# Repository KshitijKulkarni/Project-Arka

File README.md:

# Project-Arka
The project code base is split on two folders
1. Microcontroller Code - All code that will be run/tested on microcontrollers (Teensy 4.1, Arduino UNO etc)
2. Ground Control Code - All code that will be run on a system external to the engine (includes code for the GUI)

## Microcontroller Code
The files in this folder are sorted as follows
```
Microcontroller Code
├── moduleTestCodes
└── <microcontrollerBoardname>
    ├── <microcontrollerBoardname>.ino
    └── src
        ├── HelperModule1
        │   ├── HelperModule1.h
        │   └── HelperModule1.cpp
        ├── HelperModule2
        │   ├── HelperModule2.h
        │   └── HelperModule2.cpp
        └── HelperModule3
            ├── HelperModule3.h
            └── HelperModule3.cpp
```

The moduleTestCodes directory contains code for testing individual sensor/motor modules, which are not directly suitable for reuse in the final project.

## Ground Control Code

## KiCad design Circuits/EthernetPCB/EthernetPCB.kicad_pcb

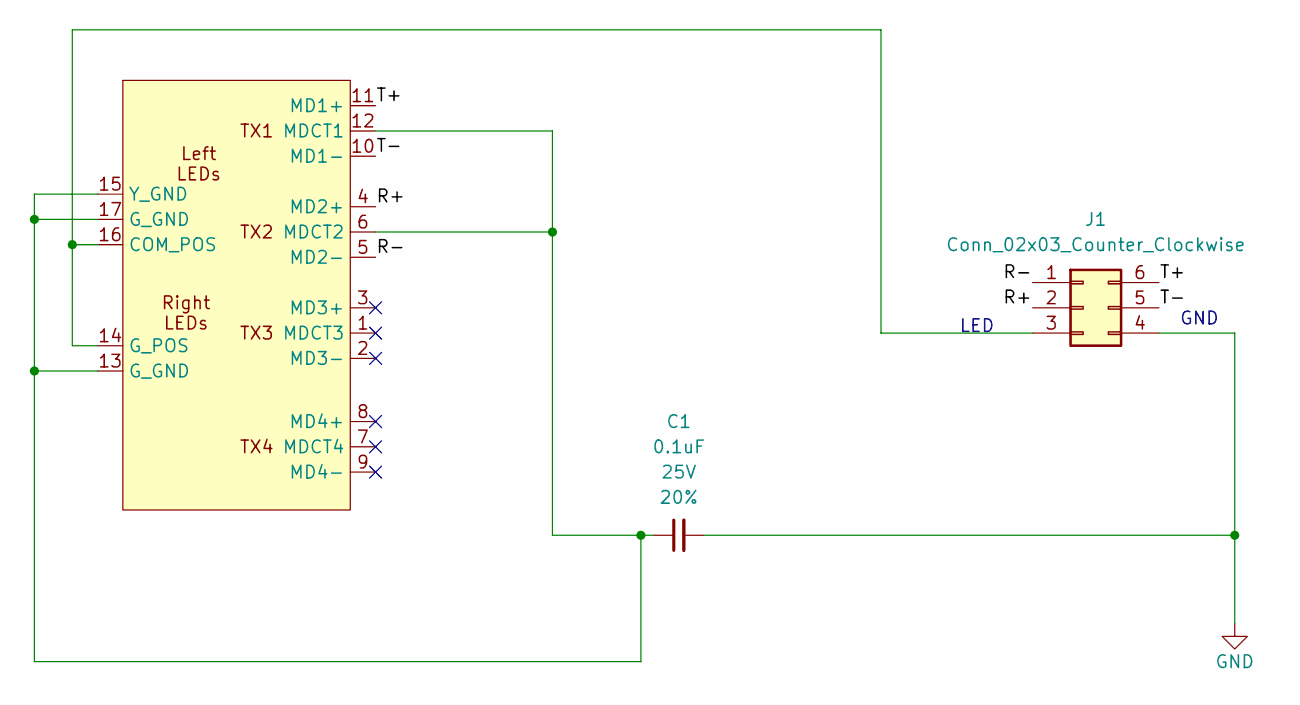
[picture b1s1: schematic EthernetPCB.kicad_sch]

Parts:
C1: 0.1uF; C_Disc_D3.0mm_W2.0mm_P2.50mm; Voltage 25V; Tolerance 20%
J1: Conn_02x03_Counter_Clockwise; PinHeader_2x03_P2.54mm_Vertical
U1: LINK-PP LPJK7003B97NL

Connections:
/R+: J1.2, U1.4 (MD2+)
/R-: J1.1, U1.5 (MD2-)
/T+: J1.6, U1.11 (MD1+)
/T-: J1.5, U1.10 (MD1-)
GND: C1.2, J1.4
unnamed: J1.3, U1.14 (G_POS), U1.16 (COM_POS)
unnamed: C1.1, U1.6 (MDCT2), U1.12 (MDCT1), U1.13 (G_GND), U1.15 (Y_GND), U1.17 (G_GND)

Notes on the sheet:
LED
GND

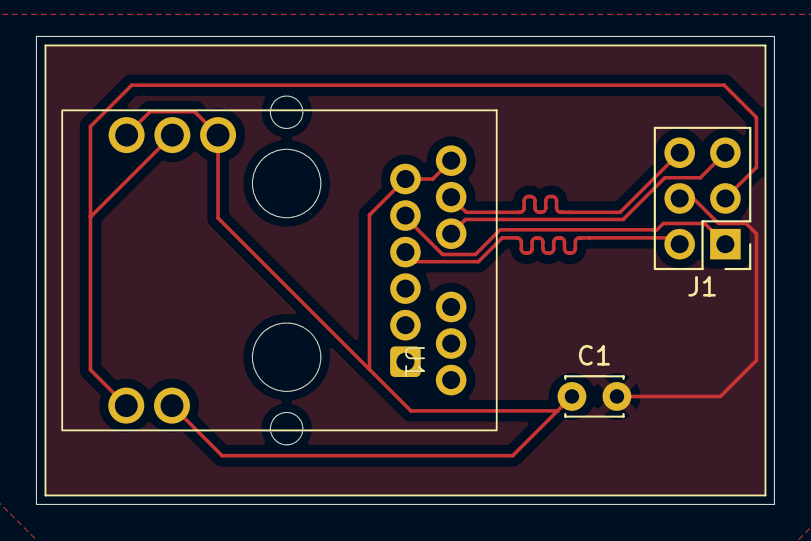
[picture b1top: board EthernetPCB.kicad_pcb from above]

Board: 2 copper layers, 41.0 x 26.0 mm, 3 parts (0 on the bottom side), 7 nets.

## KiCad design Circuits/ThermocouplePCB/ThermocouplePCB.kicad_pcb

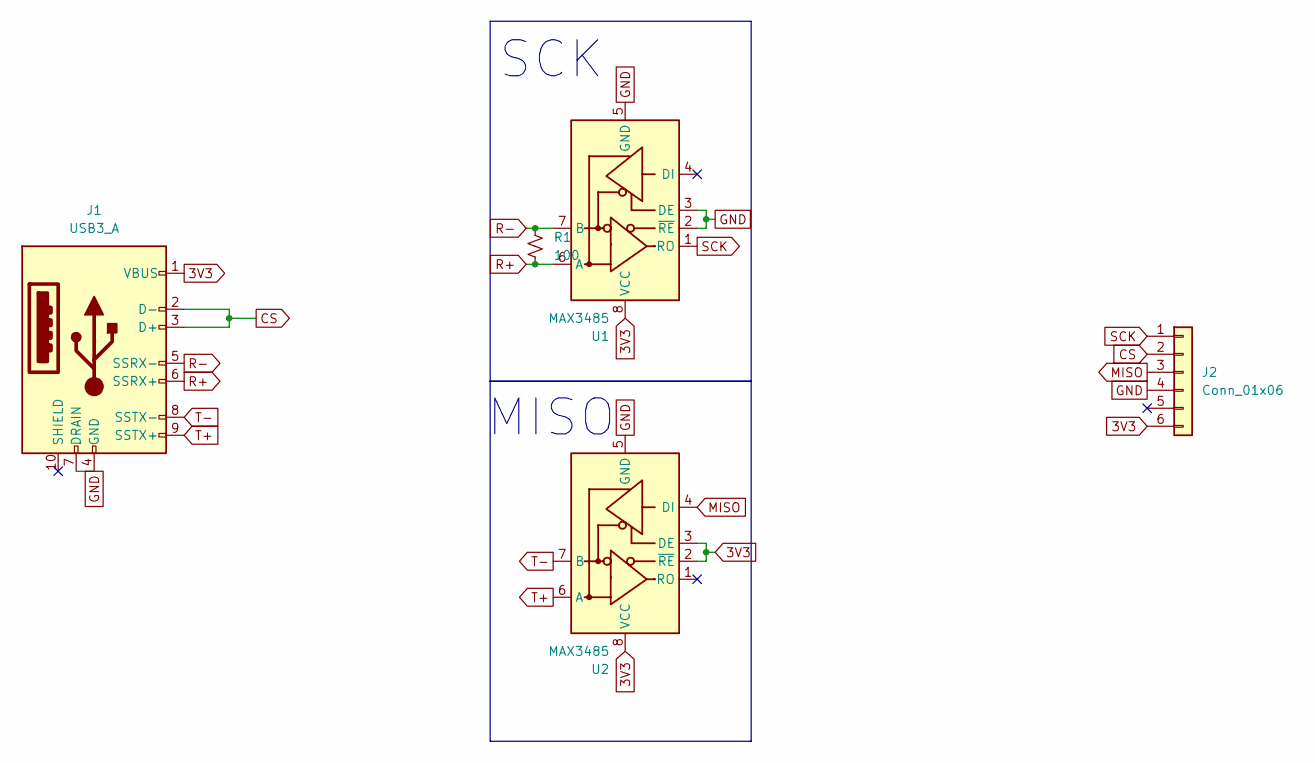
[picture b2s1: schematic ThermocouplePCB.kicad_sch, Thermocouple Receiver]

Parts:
J1: USB3_A; SAMTEC_USB3-A-S-F-TH
J2: Conn_01x06; PinSocket_1x06_P2.54mm_Vertical
R1: 100; R_Axial_DIN0207_L6.3mm_D2.5mm_P7.62mm_Horizontal
U1, U2: MAX3485; SOIC-8_3.9x4.9mm_P1.27mm

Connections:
3V3: J1.1 (VBUS), J2.6, U1.8 (VCC), U2.2 (~RE), U2.3 (DE), U2.8 (VCC)
CS: J1.2 (D-), J1.3 (D+), J2.2
GND: J1.4 (GND), J1.7 (DRAIN), J2.4, U1.2 (~RE), U1.3 (DE), U1.5 (GND), U2.5 (GND)
MISO: J2.3, U2.4 (DI)
R+: J1.6 (SSRX+), R1.1, U1.6 (A)
R-: J1.5 (SSRX-), R1.2, U1.7 (B)
SCK: J2.1, U1.1 (RO)
T+: J1.9 (SSTX+), U2.6 (A)
T-: J1.8 (SSTX-), U2.7 (B)

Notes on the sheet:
SCK
MISO

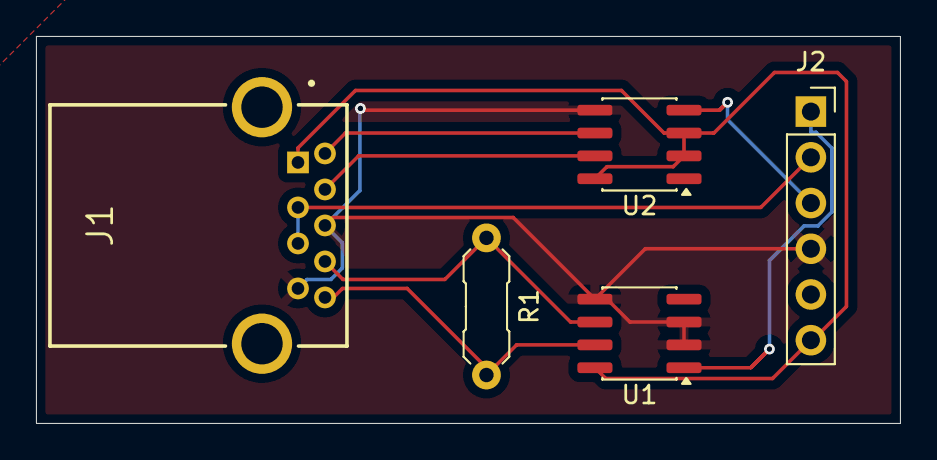
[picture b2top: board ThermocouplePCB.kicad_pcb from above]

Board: 2 copper layers, 48.0 x 21.5 mm, 5 parts (0 on the bottom side), 9 nets.

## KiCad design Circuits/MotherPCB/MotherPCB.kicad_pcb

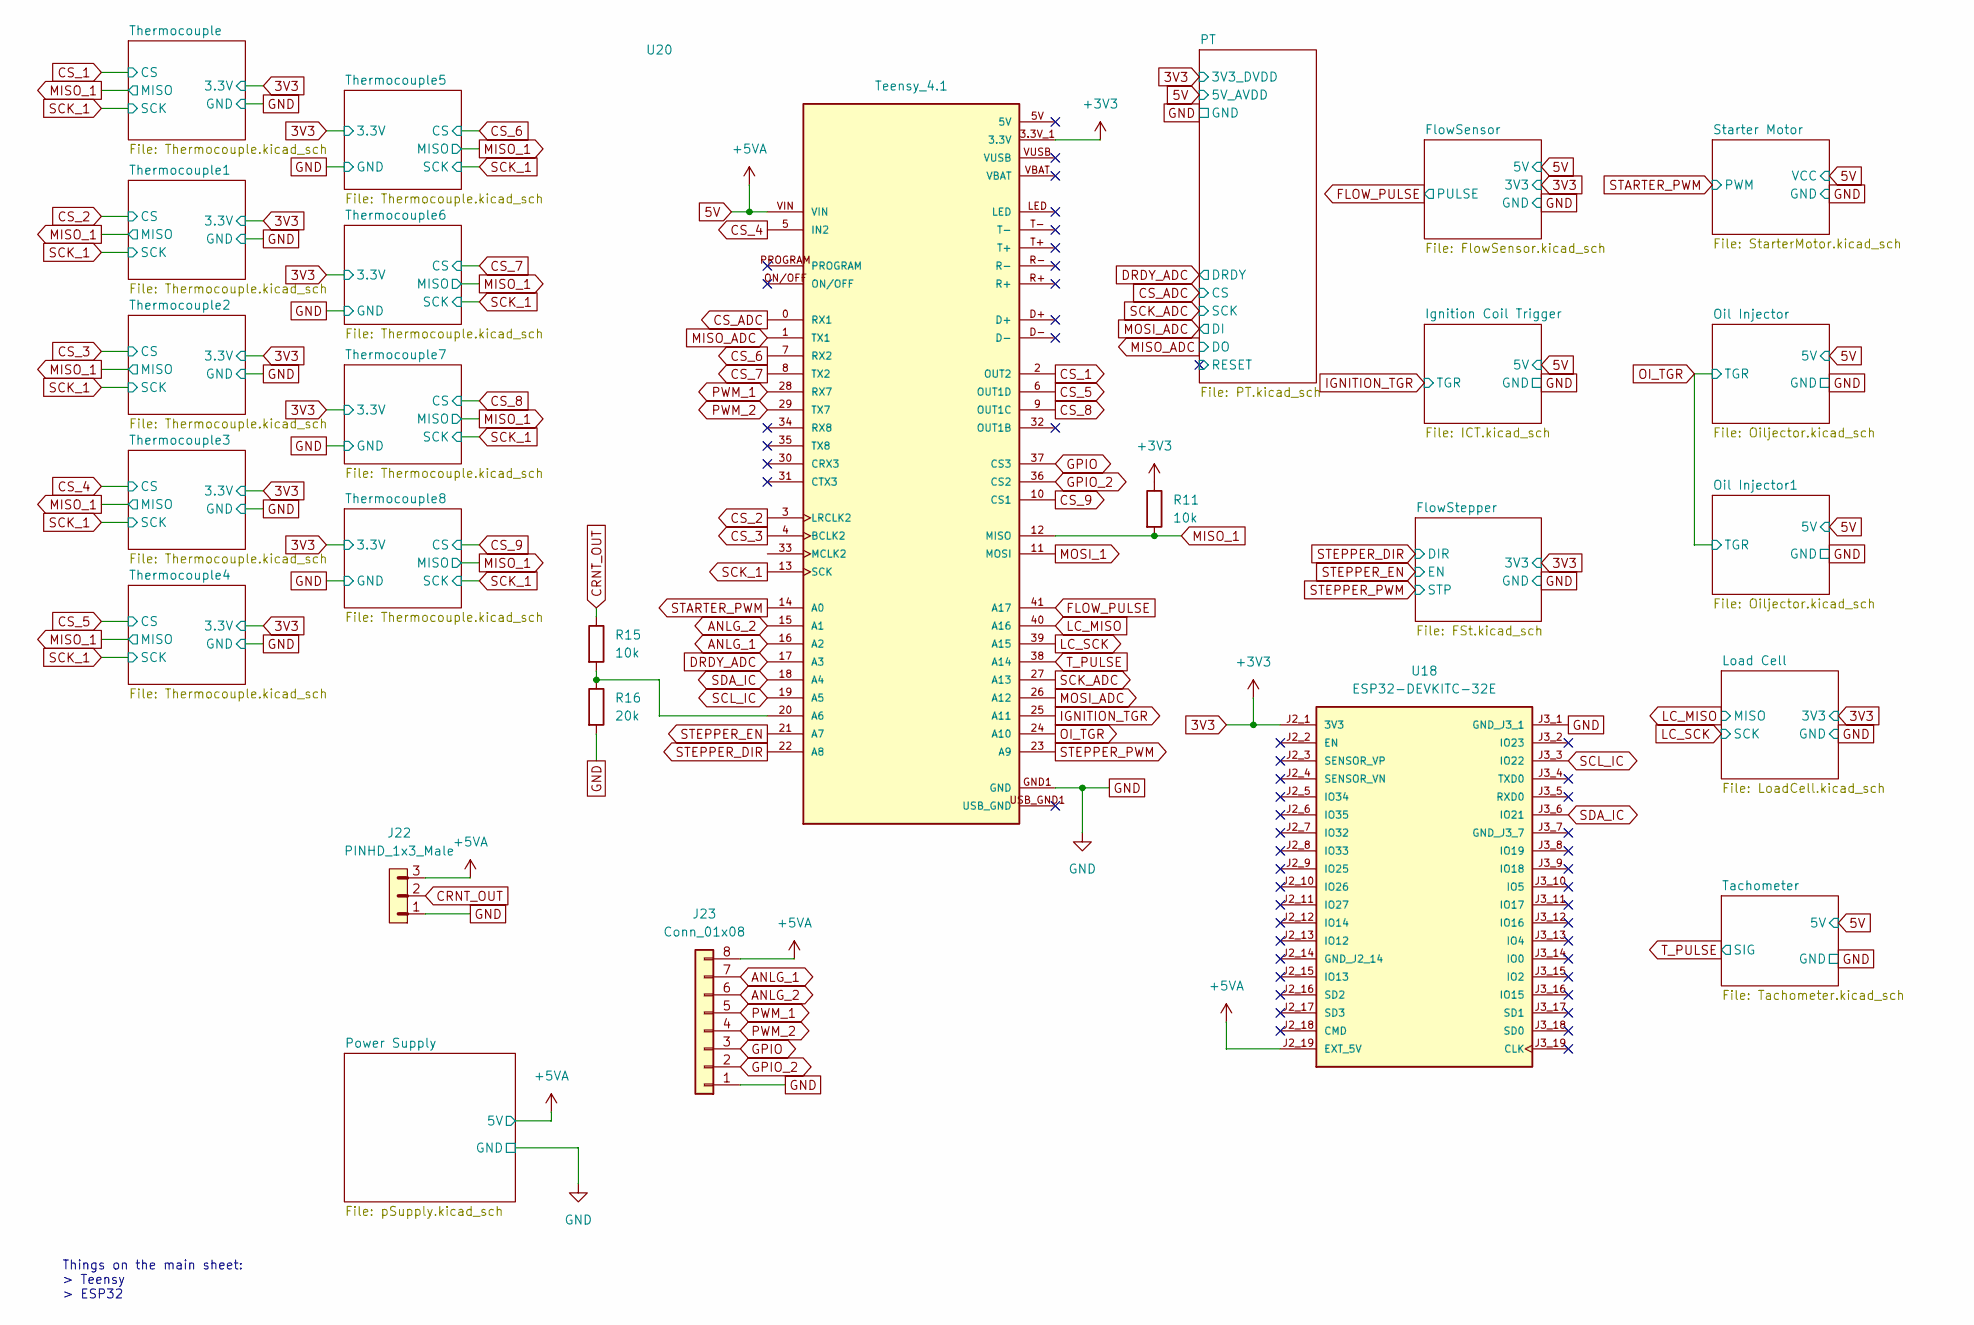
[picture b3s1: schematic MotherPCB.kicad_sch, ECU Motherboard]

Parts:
J22: PINHD_1x3_Male; PinHeader_1x03_P2.54mm_Vertical
J23: Conn_01x08; PinHeader_1x08_P2.54mm_Vertical
R11, R15: 10k; R_Axial_DIN0207_L6.3mm_D2.5mm_P7.62mm_Horizontal
R16: 20k; R_Axial_DIN0207_L6.3mm_D2.5mm_P7.62mm_Horizontal
U18: ESP32-DEVKITC-32E; MODULE_ESP32-DEVKITC-32E; PARTREV 1.4
U20: Teensy_4.1; PARTREV 4.1

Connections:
3V3: R11.1, U18.J2_1 (3V3), U20.3.3V_1 (3.3V), U20.3.3V_2 (3.3V), U20.3.3V_3 (3.3V); also elsewhere on the board
5V: J22.3, J23.8, U18.J2_19 (EXT_5V), U20.VIN; also elsewhere on the board
ANLG_1: J23.7, U20.16 (A2)
ANLG_2: J23.6, U20.15 (A1)
CRNT_OUT: J22.2, R15.1
CS_1: U20.2 (OUT2); also elsewhere on the board
CS_2: U20.3 (LRCLK2); also elsewhere on the board
CS_3: U20.4 (BCLK2); also elsewhere on the board
CS_4: U20.5 (IN2); also elsewhere on the board
CS_5: U20.6 (OUT1D); also elsewhere on the board
CS_6: U20.7 (RX2); also elsewhere on the board
CS_7: U20.8 (TX2); also elsewhere on the board
CS_8: U20.9 (OUT1C); also elsewhere on the board
CS_9: U20.10 (CS1); also elsewhere on the board
CS_ADC: U20.0 (RX1); also elsewhere on the board
DRDY_ADC: U20.17 (A3); also elsewhere on the board
FLOW_PULSE: U20.41 (A17); also elsewhere on the board
GND: J22.1, J23.1, R16.2, U18.J3_1 (GND_J3_1), U20.GND1 (GND), U20.GND2 (GND), U20.GND3 (GND), U20.GND4 (GND), U20.GND5 (GND); also elsewhere on the board
GPIO: J23.3, U20.37 (CS3)
GPIO_2: J23.2, U20.36 (CS2)
IGNITION_TGR: U20.25 (A11); also elsewhere on the board
LC_MISO: U20.40 (A16); also elsewhere on the board
LC_SCK: U20.39 (A15); also elsewhere on the board
MISO_1: R11.2, U20.12 (MISO); also elsewhere on the board
MISO_ADC: U20.1 (TX1); also elsewhere on the board
MOSI_1: U20.11 (MOSI)
MOSI_ADC: U20.26 (A12); also elsewhere on the board
unnamed: R15.2, R16.1, U20.20 (A6)
OI_TGR: U20.24 (A10); also elsewhere on the board
PWM_1: J23.5, U20.28 (RX7)
PWM_2: J23.4, U20.29 (TX7)
SCK_1: U20.13 (SCK); also elsewhere on the board
SCK_ADC: U20.27 (A13); also elsewhere on the board
SCL_IC: U18.J3_3 (IO22), U20.19 (A5)
SDA_IC: U18.J3_6 (IO21), U20.18 (A4)
STARTER_PWM: U20.14 (A0); also elsewhere on the board
STEPPER_DIR: U20.22 (A8); also elsewhere on the board
STEPPER_EN: U20.21 (A7); also elsewhere on the board
STEPPER_PWM: U20.23 (A9); also elsewhere on the board
T_PULSE: U20.38 (A14); also elsewhere on the board

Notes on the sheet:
Things on the main sheet: > Teensy > ESP32

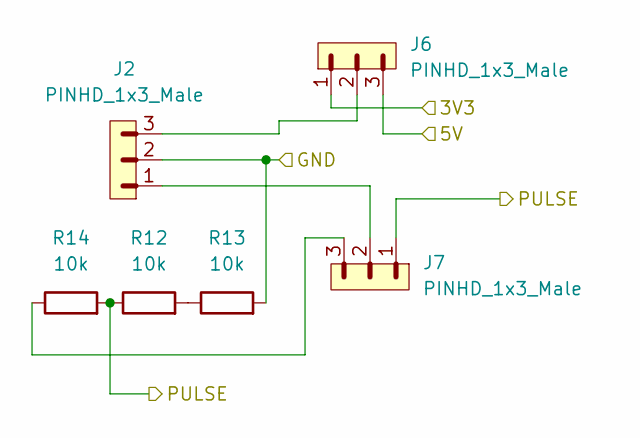
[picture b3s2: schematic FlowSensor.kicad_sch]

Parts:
J2, J6, J7: PINHD_1x3_Male; PinHeader_1x03_P2.54mm_Vertical
R12, R13, R14: 10k; R_Axial_DIN0207_L6.3mm_D2.5mm_P7.62mm_Horizontal

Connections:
3V3: J6.1; also elsewhere on the board
5V: J6.3; also elsewhere on the board
FLOW_PULSE: J7.1, R12.1, R14.2; also elsewhere on the board
GND: J2.2, R13.2; also elsewhere on the board
unnamed: J2.1, J7.2
unnamed: J2.3, J6.2
unnamed: J7.3, R14.1
unnamed: R12.2, R13.1

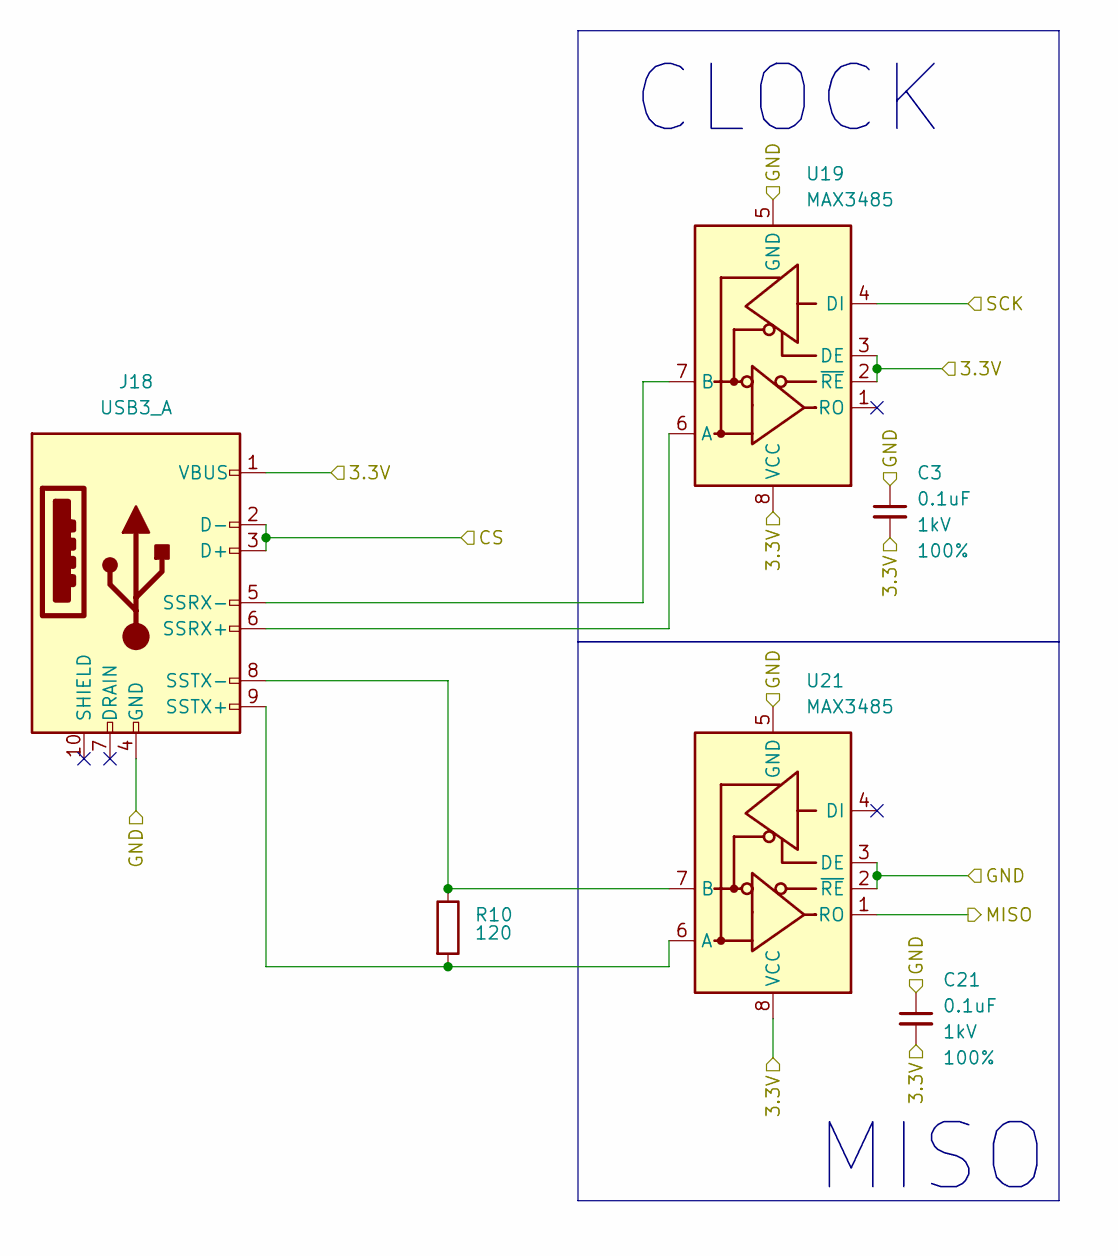
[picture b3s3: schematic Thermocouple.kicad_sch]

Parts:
C3, C21: 0.1uF; C_Disc_D5.0mm_W2.5mm_P5.00mm; Voltage 1kV; Tolerance 100%
J18: USB3_A; SAMTEC_USB3-A-S-F-TH
R10: 120; R_Axial_DIN0207_L6.3mm_D2.5mm_P7.62mm_Horizontal
U19, U21: MAX3485; SOIC-8_3.9x4.9mm_P1.27mm

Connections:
3V3: C3.2, C21.2, J18.1 (VBUS), U19.2 (~RE), U19.3 (DE), U19.8 (VCC), U21.8 (VCC); also elsewhere on the board
CS_1: J18.2 (D-), J18.3 (D+); also elsewhere on the board
GND: C3.1, C21.1, J18.4 (GND), U19.5 (GND), U21.2 (~RE), U21.3 (DE), U21.5 (GND); also elsewhere on the board
MISO_1: U21.1 (RO); also elsewhere on the board
unnamed: J18.6 (SSRX+), U19.6 (A)
unnamed: J18.5 (SSRX-), U19.7 (B)
unnamed: J18.9 (SSTX+), R10.2, U21.6 (A)
unnamed: J18.8 (SSTX-), R10.1, U21.7 (B)
SCK_1: U19.4 (DI); also elsewhere on the board

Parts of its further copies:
C4, C5, C6, C7, C8, C9, C10, C11, C12, C13, C14, C15, C16, C17, C18, C20: 0.1uF; C_Disc_D5.0mm_W2.5mm_P5.00mm; Voltage 1kV; Tolerance 100%
J1, J9, J10, J11, J12, J13, J14, J15: USB3_A; SAMTEC_USB3-A-S-F-TH
R1, R2, R3, R4, R5, R6, R7, R8: 120; R_Axial_DIN0207_L6.3mm_D2.5mm_P7.62mm_Horizontal
U2, U3, U4, U5, U6, U7, U8, U9, U10, U11, U12, U13, U14, U15, U16, U17: MAX3485; SOIC-8_3.9x4.9mm_P1.27mm

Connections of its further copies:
3V3: C4.2, C5.2, C6.2, C7.2, C8.2, C9.2, C10.2, C11.2, C12.2, C13.2, C14.2, C15.2, C16.2, C17.2, C18.2, C20.2, J1.1 (VBUS), J9.1 (VBUS), J10.1 (VBUS), J11.1 (VBUS), J12.1 (VBUS), J13.1 (VBUS), J14.1 (VBUS), J15.1 (VBUS), U2.2 (~RE), U2.3 (DE), U2.8 (VCC), U3.8 (VCC), U4.2 (~RE), U4.3 (DE), U4.8 (VCC), U5.8 (VCC), U6.2 (~RE), U6.3 (DE), U6.8 (VCC), U7.8 (VCC), U8.2 (~RE), U8.3 (DE), U8.8 (VCC), U9.8 (VCC), U10.2 (~RE), U10.3 (DE), U10.8 (VCC), U11.8 (VCC), U12.2 (~RE), U12.3 (DE), U12.8 (VCC), U13.8 (VCC), U14.2 (~RE), U14.3 (DE), U14.8 (VCC), U15.8 (VCC), U16.2 (~RE), U16.3 (DE), U16.8 (VCC), U17.8 (VCC); also elsewhere on the board
CS_2: J9.2 (D-), J9.3 (D+); also elsewhere on the board
CS_3: J1.2 (D-), J1.3 (D+); also elsewhere on the board
CS_4: J10.2 (D-), J10.3 (D+); also elsewhere on the board
CS_5: J11.2 (D-), J11.3 (D+); also elsewhere on the board
CS_6: J12.2 (D-), J12.3 (D+); also elsewhere on the board
CS_7: J13.2 (D-), J13.3 (D+); also elsewhere on the board
CS_8: J14.2 (D-), J14.3 (D+); also elsewhere on the board
CS_9: J15.2 (D-), J15.3 (D+); also elsewhere on the board
GND: C4.1, C5.1, C6.1, C7.1, C8.1, C9.1, C10.1, C11.1, C12.1, C13.1, C14.1, C15.1, C16.1, C17.1, C18.1, C20.1, J1.4 (GND), J9.4 (GND), J10.4 (GND), J11.4 (GND), J12.4 (GND), J13.4 (GND), J14.4 (GND), J15.4 (GND), U2.5 (GND), U3.2 (~RE), U3.3 (DE), U3.5 (GND), U4.5 (GND), U5.2 (~RE), U5.3 (DE), U5.5 (GND), U6.5 (GND), U7.2 (~RE), U7.3 (DE), U7.5 (GND), U8.5 (GND), U9.2 (~RE), U9.3 (DE), U9.5 (GND), U10.5 (GND), U11.2 (~RE), U11.3 (DE), U11.5 (GND), U12.5 (GND), U13.2 (~RE), U13.3 (DE), U13.5 (GND), U14.5 (GND), U15.2 (~RE), U15.3 (DE), U15.5 (GND), U16.5 (GND), U17.2 (~RE), U17.3 (DE), U17.5 (GND); also elsewhere on the board
MISO_1: U3.1 (RO), U5.1 (RO), U7.1 (RO), U9.1 (RO), U11.1 (RO), U13.1 (RO), U15.1 (RO), U17.1 (RO); also elsewhere on the board
unnamed: J1.6 (SSRX+), U4.6 (A)
unnamed: J1.5 (SSRX-), U4.7 (B)
unnamed: J1.9 (SSTX+), R2.2, U5.6 (A)
unnamed: J1.8 (SSTX-), R2.1, U5.7 (B)
unnamed: J9.6 (SSRX+), U2.6 (A)
unnamed: J9.5 (SSRX-), U2.7 (B)
unnamed: J9.9 (SSTX+), R1.2, U3.6 (A)
unnamed: J9.8 (SSTX-), R1.1, U3.7 (B)
unnamed: J10.6 (SSRX+), U6.6 (A)
unnamed: J10.5 (SSRX-), U6.7 (B)
unnamed: J10.9 (SSTX+), R3.2, U7.6 (A)
unnamed: J10.8 (SSTX-), R3.1, U7.7 (B)
unnamed: J11.6 (SSRX+), U8.6 (A)
unnamed: J11.5 (SSRX-), U8.7 (B)
unnamed: J11.9 (SSTX+), R4.2, U9.6 (A)
unnamed: J11.8 (SSTX-), R4.1, U9.7 (B)
unnamed: J12.6 (SSRX+), U10.6 (A)
unnamed: J12.5 (SSRX-), U10.7 (B)
unnamed: J12.9 (SSTX+), R5.2, U11.6 (A)
unnamed: J12.8 (SSTX-), R5.1, U11.7 (B)
unnamed: J13.6 (SSRX+), U12.6 (A)
unnamed: J13.5 (SSRX-), U12.7 (B)
unnamed: J13.9 (SSTX+), R6.2, U13.6 (A)
unnamed: J13.8 (SSTX-), R6.1, U13.7 (B)
unnamed: J14.6 (SSRX+), U14.6 (A)
unnamed: J14.5 (SSRX-), U14.7 (B)
unnamed: J14.9 (SSTX+), R7.2, U15.6 (A)
unnamed: J14.8 (SSTX-), R7.1, U15.7 (B)
unnamed: J15.6 (SSRX+), U16.6 (A)
unnamed: J15.5 (SSRX-), U16.7 (B)
unnamed: J15.9 (SSTX+), R8.2, U17.6 (A)
unnamed: J15.8 (SSTX-), R8.1, U17.7 (B)
SCK_1: U2.4 (DI), U4.4 (DI), U6.4 (DI), U8.4 (DI), U10.4 (DI), U12.4 (DI), U14.4 (DI), U16.4 (DI); also elsewhere on the board

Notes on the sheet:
CLOCK
MISO

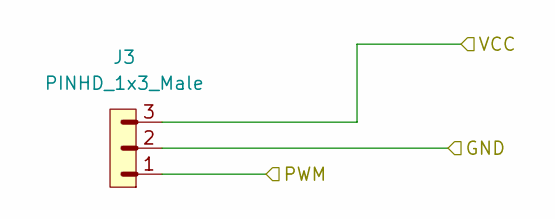
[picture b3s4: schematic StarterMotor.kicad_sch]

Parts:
J3: PINHD_1x3_Male; PinHeader_1x03_P2.54mm_Vertical

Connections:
5V: J3.3; also elsewhere on the board
GND: J3.2; also elsewhere on the board
STARTER_PWM: J3.1; also elsewhere on the board

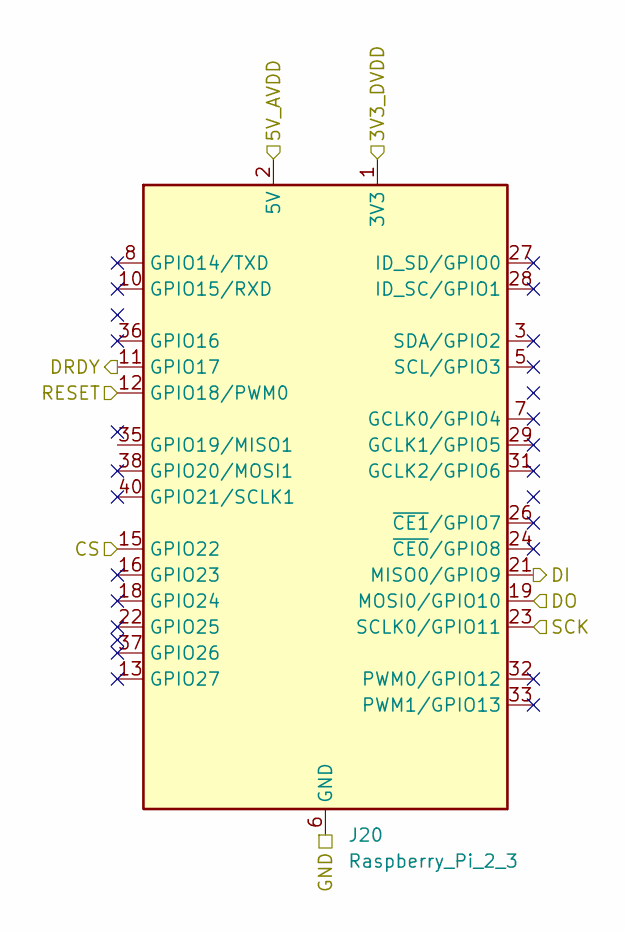
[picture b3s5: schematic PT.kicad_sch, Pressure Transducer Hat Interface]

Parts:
J20: Raspberry_Pi_2_3; PinHeader_2x20_P2.54mm_Vertical

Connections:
3V3: J20.1 (3V3), J20.17 (3V3); also elsewhere on the board
5V: J20.2 (5V), J20.4 (5V); also elsewhere on the board
/PT/RESET: J20.12 (GPIO18/PWM0)
CS_ADC: J20.15 (GPIO22); also elsewhere on the board
DRDY_ADC: J20.11 (GPIO17); also elsewhere on the board
GND: J20.6 (GND), J20.9 (GND), J20.14 (GND), J20.20 (GND), J20.25 (GND), J20.30 (GND), J20.34 (GND), J20.39 (GND); also elsewhere on the board
MISO_ADC: J20.19 (MOSI0/GPIO10); also elsewhere on the board
MOSI_ADC: J20.21 (MISO0/GPIO9); also elsewhere on the board
SCK_ADC: J20.23 (SCLK0/GPIO11); also elsewhere on the board

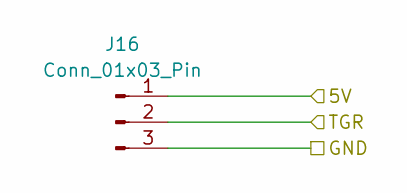
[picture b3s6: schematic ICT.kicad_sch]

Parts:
J16: Conn_01x03_Pin; PinHeader_1x03_P2.54mm_Vertical

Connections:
5V: J16.1; also elsewhere on the board
GND: J16.3; also elsewhere on the board
IGNITION_TGR: J16.2; also elsewhere on the board

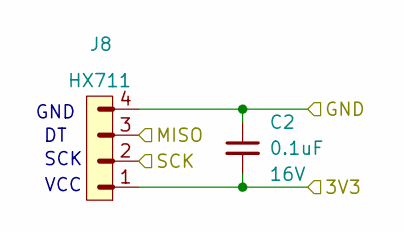
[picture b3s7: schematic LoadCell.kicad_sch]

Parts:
C2: 0.1uF; C_Disc_D5.0mm_W2.5mm_P5.00mm; Voltage 16V; Tolerance 10%
J8: HX711; PinHeader_1x04_P2.54mm_Vertical

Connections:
3V3: C2.2, J8.1; also elsewhere on the board
GND: C2.1, J8.4; also elsewhere on the board
LC_MISO: J8.3; also elsewhere on the board
LC_SCK: J8.2; also elsewhere on the board

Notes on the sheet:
SCK
GND
VCC

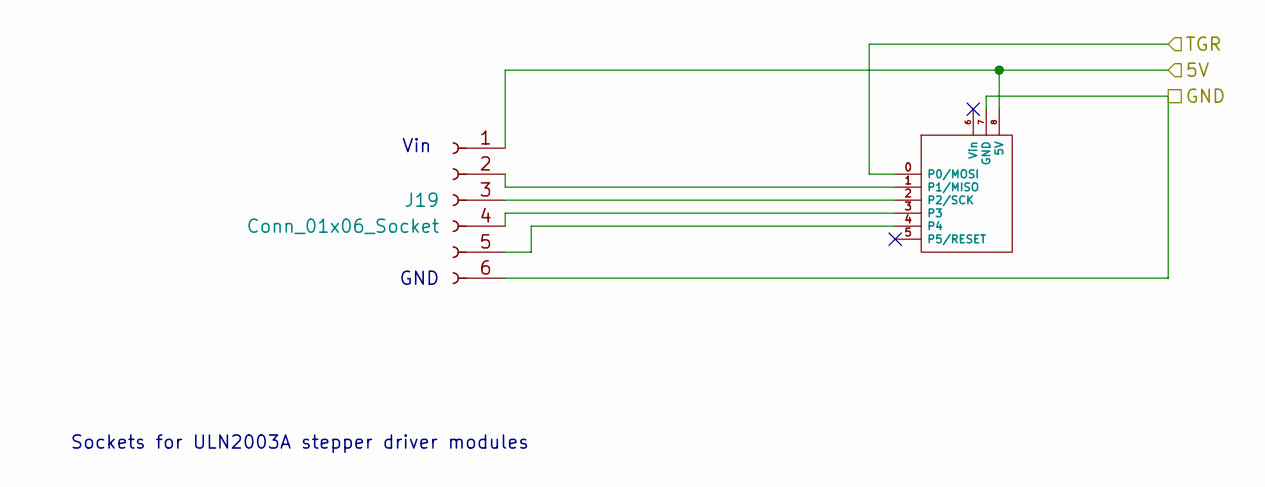
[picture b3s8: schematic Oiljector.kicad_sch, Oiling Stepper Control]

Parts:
I1: Digispark_ATTiny85_Headers
J19: Conn_01x06_Socket; PinHeader_1x06_P2.54mm_Vertical

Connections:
5V: I1.8 (5V), J19.1; also elsewhere on the board
GND: I1.7 (GND), J19.6; also elsewhere on the board
unnamed: I1.1 (P1/MISO), J19.2
unnamed: I1.2 (P2/SCK), J19.3
unnamed: I1.3, J19.4
unnamed: I1.4, J19.5
OI_TGR: I1.0 (P0/MOSI); also elsewhere on the board

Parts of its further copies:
I2: Digispark_ATTiny85_Headers
J17: Conn_01x06_Socket; PinHeader_1x06_P2.54mm_Vertical

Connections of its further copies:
5V: I2.8 (5V), J17.1; also elsewhere on the board
GND: I2.7 (GND), J17.6; also elsewhere on the board
unnamed: I2.1 (P1/MISO), J17.2
unnamed: I2.2 (P2/SCK), J17.3
unnamed: I2.3, J17.4
unnamed: I2.4, J17.5
OI_TGR: I2.0 (P0/MOSI); also elsewhere on the board

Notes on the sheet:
Sockets for ULN2003A stepper driver modules
GND
Vin

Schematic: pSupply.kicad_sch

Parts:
J21: XT60-M; AMASS_XT60-M; PARTREV V1.2
P1: LM2596 Module

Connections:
5V: P1.1 (VO); also elsewhere on the board
GND: P1.2 (GND); also elsewhere on the board
unnamed: J21.N (NEG), P1.4 (GND)
unnamed: J21.P (POS), P1.3 (VI)

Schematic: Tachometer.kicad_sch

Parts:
J4: Conn_01x03_Pin; PinHeader_1x03_P2.54mm_Vertical
R9, R20, R21: 10k; R_Axial_DIN0207_L6.3mm_D2.5mm_P7.62mm_Horizontal

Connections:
5V: J4.2; also elsewhere on the board
GND: J4.3, R9.2; also elsewhere on the board
unnamed: J4.1, R21.1
unnamed: R9.1, R20.2
T_PULSE: R20.1, R21.2; also elsewhere on the board

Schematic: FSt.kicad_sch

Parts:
J5: PINHD_1x5_Male; PinHeader_1x05_P2.54mm_Vertical

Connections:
3V3: J5.5; also elsewhere on the board
GND: J5.4; also elsewhere on the board
STEPPER_DIR: J5.2; also elsewhere on the board
STEPPER_EN: J5.3; also elsewhere on the board
STEPPER_PWM: J5.1; also elsewhere on the board

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
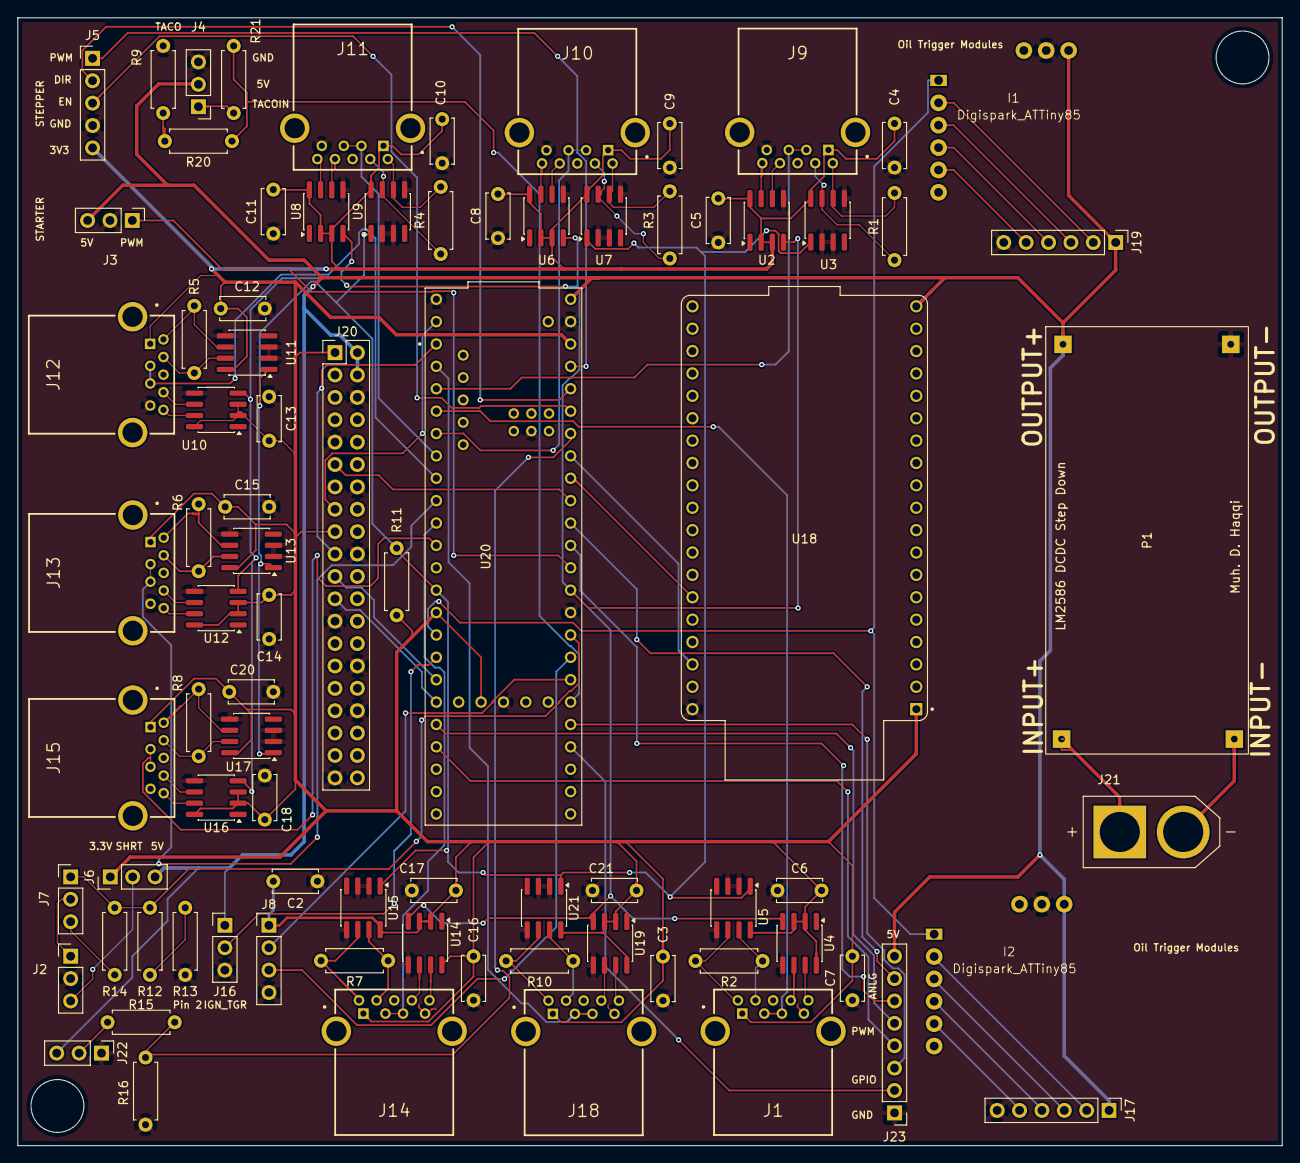
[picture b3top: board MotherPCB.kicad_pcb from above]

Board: 2 copper layers, 143.5 x 128.0 mm, 83 parts (0 on the bottom side), 91 nets.

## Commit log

2025-10-30 Add descriptions for Python and Arduino files
2025-10-30 Next commit after initial commit
2025-10-30 Second point five commit
2025-11-04 UI Commit
    First iteration of neo-gui
2025-11-04 Restructured Codebase
2025-11-30 Added ESPComms Class and data transmission capability
2025-12-01 Added Tachometer module and converted project to a PlatformIO project
2025-12-02 The first commit with the new, flutter GUI
    The flutter project was created with android studio. You can open it, access it and edit it. The project folder is flutterprojs under the Flutter directory.
2025-12-03 A little more code restructuring to suit PlatformIO
2025-12-03 my ocd wouldnt let me not restructure those folders
2025-12-03 hang on Im debugging a github problem
2025-12-03 okay debugging complete
2025-12-03 Cleaning up after the move to Ground Control Code
    I rebuilt the UI to ensure nothing was broken. This regenerated some cache files and deleted others. Now it's development ready in the new directory
2025-12-08 Added I2C receive code on Thambi
2025-12-08 Added I2C comms on Guru
2025-12-09 Some renaming, and template for Anna code
2025-12-09 Changed prefferences to match the ESP devkit being used
2025-12-09 Added Anna code for ESPNow comms
2025-12-09 Thambi -> Anna communication is working.
    Thambi just forwards Guru's code to Anna
2025-12-09 Added Code for Anna to receive data from Thambi
2025-12-10 Got the GUI talking nicely to Anna
2025-12-10 UI now shows received values
2025-12-10 2-Way comms code before debugging
2025-12-10 Debugging 1
2025-12-10 2-Way comms working
2025-12-10 2-Way Comms working (Anna)
2026-01-23 Added FreeRTOS, and code for data streaming with tachometer reading
2026-01-25 KiCad push 1
2026-01-25 The PCB work is now underway!
2026-01-25 Done for the night
    Finished up thermocouple differential communication and every other module apart from PTs and Oil Injector.
    Good night.
    oh wait
    It's 4:00 am.
    Good morning
2026-01-26 cleaned up the lib folder of microcontroller code
2026-01-26 Added footprint for ATTiny85 module, added schematic for oil injector circuit
2026-01-26 Added Teensy and some labels to the schematic
2026-01-28 Schematic Finished
2026-01-28 Fixed some broken footprints
2026-01-29 pcb completed with a clean DRC
    first one it is let us pray it works
2026-01-29 PCB v2 um
2026-02-04 This commit comprises of multiple changes 1. Final MotherPCB (Redesigned by Akshay, only pushed to GitHub by me) 2. PCB for interfacing with the Ethernet MagJack 3. Code for Pressure Transducer data 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
2026-02-06 Thermocouple Satellite PCB Added
2026-02-09 Final output in thermocouple and ethernet pcb
    Verified. Ground plane added. All systems normal.
2026-02-11 Added some headers and Flow Sensor code
2026-02-15 Added code for the fuel sensor, and headers for fuel controller
2026-02-17 Added code for fuel sensor classand fuel controller class (only PID implementation included), stepper motor control pending
2026-03-05 Added Stepper motor control
2026-03-05 Added Starter Motor module, listed control sequence tasks (tasks yet to be populated)
2026-03-07 Added Control Sequence Tasks
2026-03-07 Removed FreeRTOS from the lib folder
